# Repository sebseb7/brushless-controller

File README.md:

brushless-controller
====================

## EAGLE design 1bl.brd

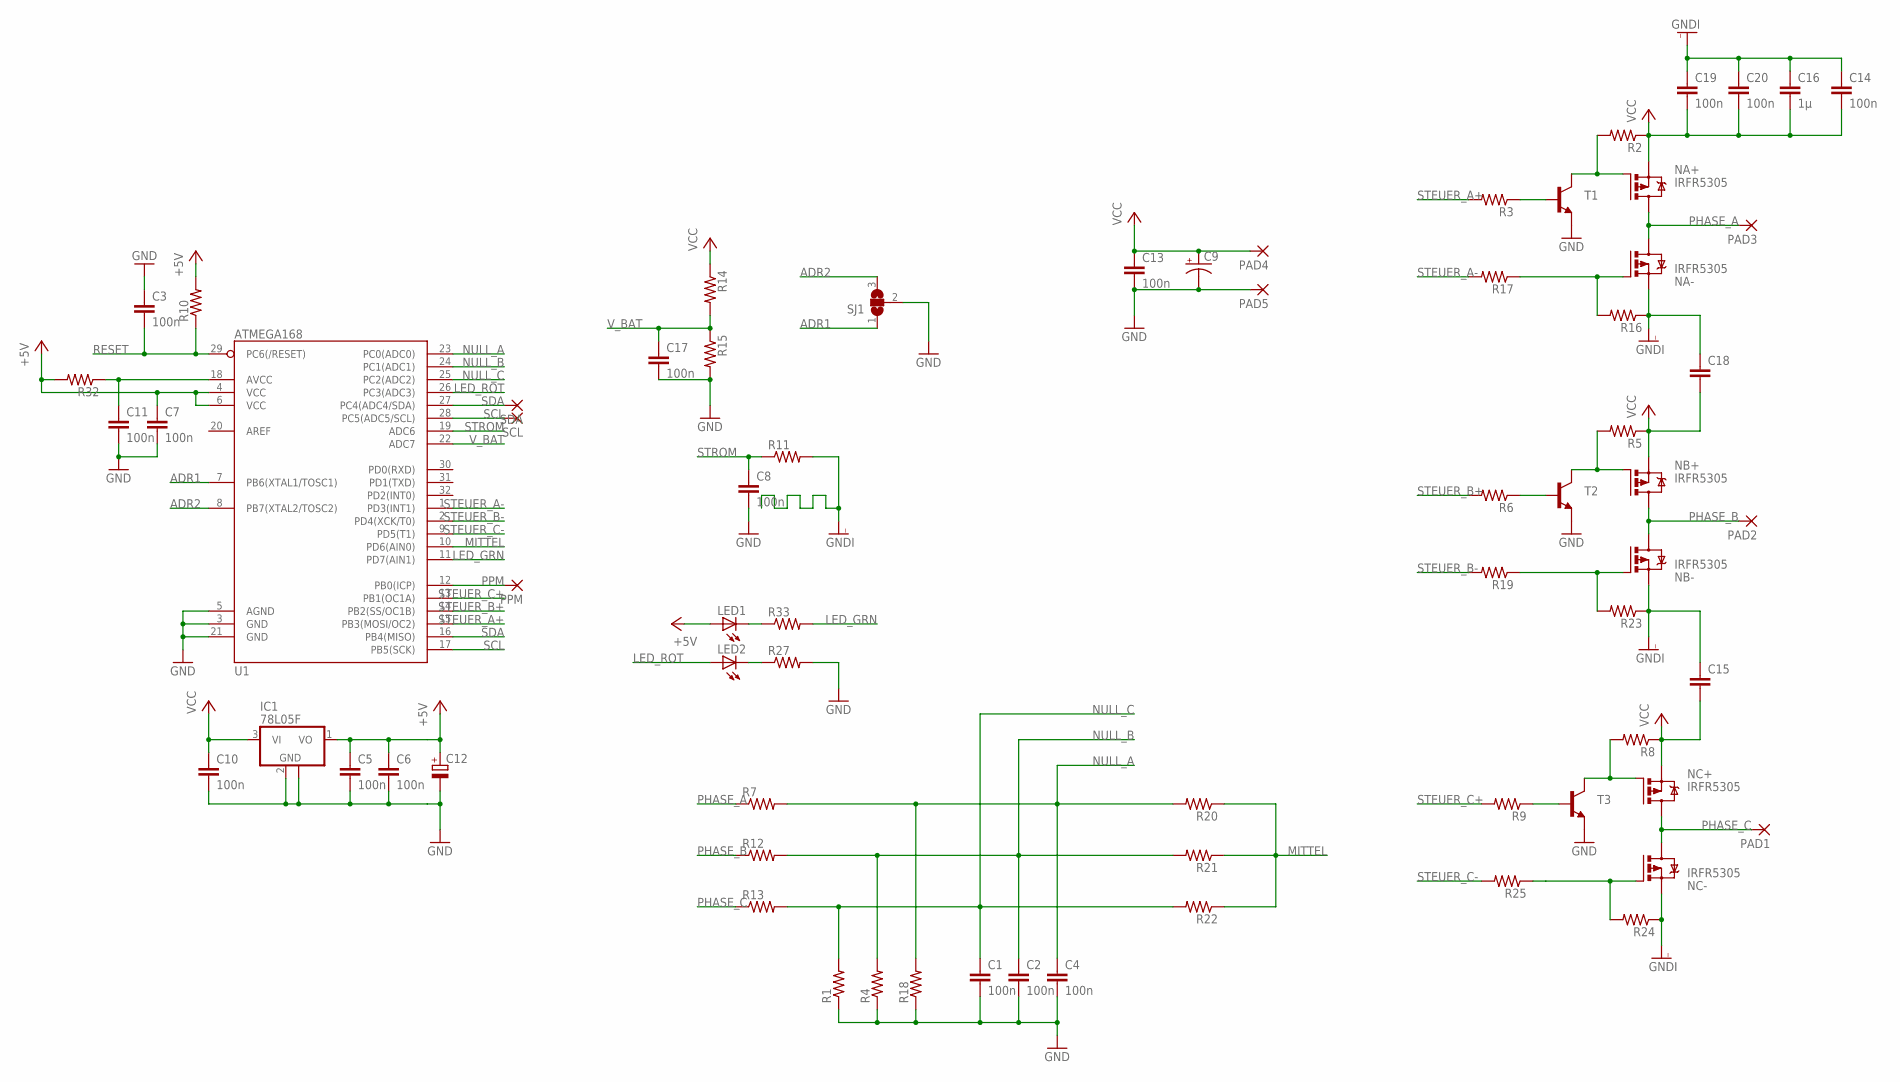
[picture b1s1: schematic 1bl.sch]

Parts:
C1, C2, C3, C4, C5, C6, C7, C8, C10, C11, C13, C14, C17, C19, C20: 100n; 0805
C9: CAP_POLPTH4; CPOL-RADIAL-1000UF-25V
C12: CPOL-EUB; PANASONIC_B
C15, C18: CAP0805; 0805
C16: 1µ; 0805
IC1: 78L05F; SOT89
LED1, LED2: LEDCHIP-LED0805; CHIP-LED0805
NA+: IRFR5305; D-PAK_TO252AA
NA-: IRFR5305; D-PAK_TO252AA
NB+: IRFR5305; D-PAK_TO252AA
NB-: IRFR5305; D-PAK_TO252AA
NC+: IRFR5305; D-PAK_TO252AA
NC-: IRFR5305; D-PAK_TO252AA
PAD1, PAD2, PAD3, PAD4, PAD5: SMD5; SMD2,54-5,08
PPM: SMD2; SMD1,27-2,54
R1, R2, R3, R4, R5, R6, R7, R8, R9, R10, R11, R12, R13, R14, R15, R16, R17, R18, R19, R20, R21, R22, R23, R24, R25, R27, R32, R33: RESISTOR; 0805
SCL: SMD2; SMD1,27-2,54
SDA: SMD2; SMD1,27-2,54
SJ1: SJ2W; SJ_2
T1, T2, T3: TRANSISTOR_NPNSOT23; SOT23
U1: ATMEGA168; TQFP32-08

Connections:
+5V: C5.1, C6.1, C7.1, C12.+, IC1.1 (VO), LED1.A, R10.2, R32.2, U1.4 (VCC), U1.6 (VCC)
ADR1: SJ1.1, U1.7 (PB6(XTAL1/TOSC1))
ADR2: SJ1.3, U1.8 (PB7(XTAL2/TOSC2))
GND: C1.2, C2.2, C3.1, C4.2, C5.2, C6.2, C7.2, C8.2, C9.2 (-), C10.2, C11.2, C12.-, C13.2, C17.2, IC1.2 (GND), IC1.2@1 (GND), PAD5.1, R1.1, R4.1, R15.2, R18.1, R27.2, SJ1.2, T1.2 (E), T2.2 (E), T3.2 (E), U1.3 (GND), U1.5 (AGND), U1.21 (GND)
GNDI: C14.1, C15.1, C16.1, C18.1, C19.1, C20.1, NA-.3 (S), NB-.3 (S), NC-.3 (S), R11.2, R16.1, R23.1, R24.1
LED_GRN: R33.2, U1.11 (PD7(AIN1))
LED_ROT: LED2.A, U1.26 (PC3(ADC3))
MITTEL: R20.1, R21.1, R22.1, U1.10 (PD6(AIN0))
unnamed: C11.1, R32.1, U1.18 (AVCC)
unnamed: NC+.1 (G), R8.2, T3.3 (C)
unnamed: NB+.1 (G), R5.2, T2.3 (C)
unnamed: NA+.1 (G), R2.2, T1.3 (C)
unnamed: LED1.C, R33.1
unnamed: LED2.C, R27.1
unnamed: NA-.1 (G), R16.2, R17.1
unnamed: NB-.1 (G), R19.1, R23.2
unnamed: NC-.1 (G), R24.2, R25.1
unnamed: R3.1, T1.1 (B)
unnamed: R6.1, T2.1 (B)
unnamed: R9.1, T3.1 (B)
NULL_A: C4.1, R7.2, R18.2, R20.2, U1.23 (PC0(ADC0))
NULL_B: C2.1, R4.2, R12.2, R21.2, U1.24 (PC1(ADC1))
NULL_C: C1.1, R1.2, R13.2, R22.2, U1.25 (PC2(ADC2))
PHASE_A: NA+.4 (D), NA-.4 (D), PAD3.1, R7.1
PHASE_B: NB+.4 (D), NB-.4 (D), PAD2.1, R12.1
PHASE_C: NC+.4 (D), NC-.4 (D), PAD1.1, R13.1
PPM: PPM.1, U1.12 (PB0(ICP))
RESET: C3.2, R10.1, U1.29 (PC6(/RESET))
SCL: SCL.1, U1.17 (PB5(SCK)), U1.28 (PC5(ADC5/SCL))
SDA: SDA.1, U1.16 (PB4(MISO)), U1.27 (PC4(ADC4/SDA))
STEUER_A+: R3.2, U1.15 (PB3(MOSI/OC2))
STEUER_A-: R17.2, U1.1 (PD3(INT1))
STEUER_B+: R6.2, U1.14 (PB2(SS/OC1B))
STEUER_B-: R19.2, U1.2 (PD4(XCK/T0))
STEUER_C+: R9.2, U1.13 (PB1(OC1A))
STEUER_C-: R25.2, U1.9 (PD5(T1))
STROM: C8.1, R11.1, U1.19 (ADC6)
VCC: C9.1 (+), C10.1, C13.1, C14.2, C15.2, C16.2, C18.2, C19.2, C20.2, IC1.3 (VI), NA+.3 (S), NB+.3 (S), NC+.3 (S), PAD4.1, R2.1, R5.1, R8.1, R14.1
V_BAT: C17.1, R14.2, R15.1, U1.22 (ADC7)

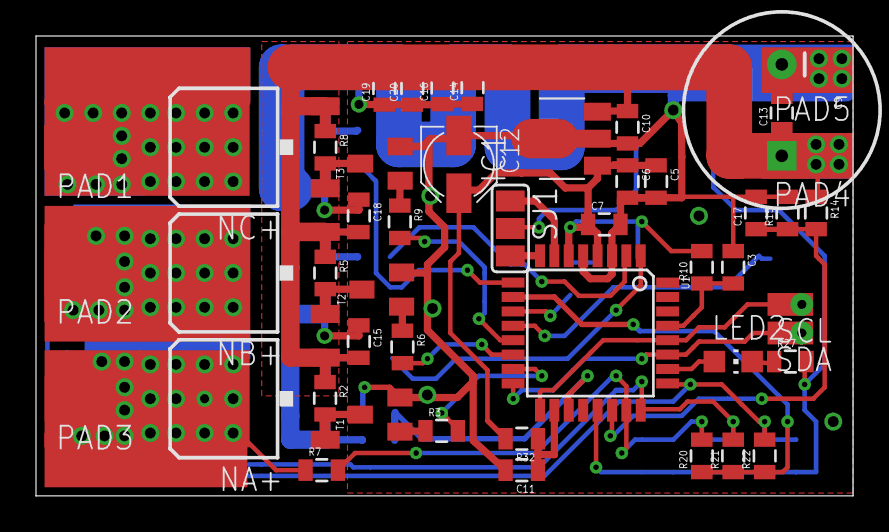
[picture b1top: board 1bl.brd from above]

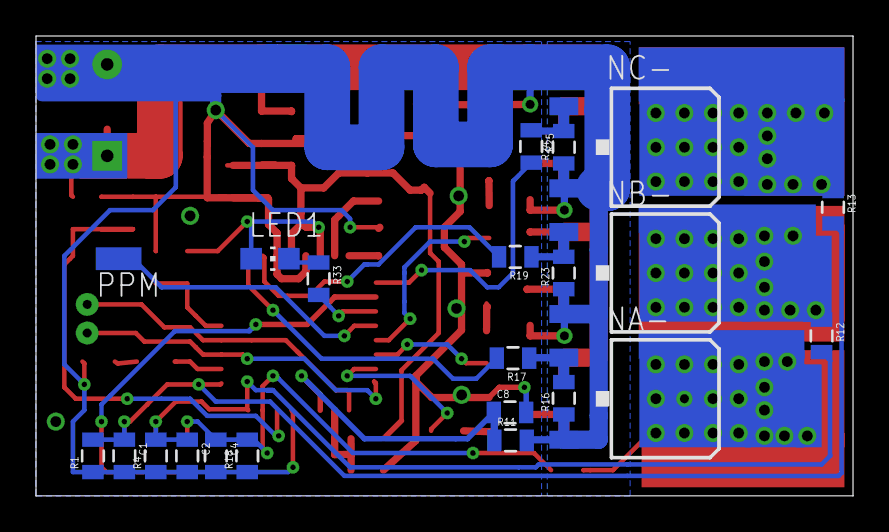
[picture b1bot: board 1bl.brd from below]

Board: 2 copper layers, 45.4 x 25.5 mm, 70 parts (22 on the bottom side), 39 nets.

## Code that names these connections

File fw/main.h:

#ifndef _MAIN_H
#define _MAIN_H

//#define MOTORADRESSE      0  // Adresse (1-4)     0 = Motoradresse über Lötjumper auf BL-Ctrl V1.1

#define MANUELL_PWM       0   // zur manuellen Vorgabe der PWM  Werte: 0-255
#define TEST_MANUELL      0   // zum Testen der Hardware ohne Kommutierungsdetektion  Werte: 0-255 (PWM)
#define TEST_SCHUB        0	  // Erzeugt ein Schubmuster        Werte: 0 = normal 1 = Test
#define POLANZAHL        12   // Anzahl der Pole (Magnete) Wird nur zur Drehzahlausgabe über Debug gebraucht
#define MAX_PWM         255
#define MIN_PWM           3
#define MIN_PPM          10   // ab hier (PPM-Signal) schaltet der Regler erst ein
#define FILTER_PPM        7   // wie stark soll das PPM-Signal gefiltert werden (Werte: 0-30)?

#define SIO_DEBUG         0   // Testwertausgaben auf der seriellen Schnittstelle
#define X3D_SIO           0	  // serielles Protokoll des X3D (38400Bd) Achtung: dann muss SIO_DEBUG = 0 sein

#define _16KHZ    // Schaltfrequenz  -- die gewünschte einkommentieren
//#define _32KHZ    // Schaltfrequenz  -- die gewünschte einkommentieren

//#define FDD6637_IRLR7843  1  // bessere MosFet bestückt? bewirkt höhere Stromgrenzen  


#ifdef _16KHZ
#if FDD_IRLR == 1                  // bessere Fets = mehr Strom zulassen
#define MAX_STROM        200  // ab ca. 20A PWM ausschalten
#define LIMIT_STROM      120  // ab ca. 12A PWM begrenzen
#else
#define MAX_STROM        130  // ab ca. 13A PWM ausschalten
#define LIMIT_STROM       65  // ab ca. 6,5A PWM begrenzen
#endif
#endif

#ifdef _32KHZ
#define MAX_STROM        130  // ab ca. 13A PWM ausschalten
#define LIMIT_STROM       50  // ab ca. 5,0A PWM begrenzen
#endif

#define SYSCLK	8000000L	//Quarz Frequenz in Hz

#define GRN_ON  {if(HwVersion < 12) PORTD |= GRUEN; else PORTD &= ~GRUEN;}
#define GRN_OFF {if(HwVersion > 11) PORTD |= GRUEN; else PORTD &= ~GRUEN;}


//Robbe Roxxy 2824-34 mit Todd 10x4,5 bei 16kHz
//PWM   Strom   Schub
//10   0,18A    21g
//20   0,30A    38g
//30   0,40A    49g
//40   0,54A    60g
//50   0,70A    83g
//60   0,95A   102g
//70   1,25A   128g
//80   1,50A   151g
//90   1,83A   175g
//100  2,25A   206g
//110  2,66A   228g
//120  3,10A   257g
//130  3,55A   278g
//140  4,00A   305g
//150  4,50A   330g
//160  5,30A   355g
//170  5,85A   387g
//180  6,40A   400g
//190  7,10A   425g
//200  7,60A   460g

//0,5A  63g 14%
//1,0A 110g 24%
//1,5A 170g 32%
//2,0A 195g 37%
//2,5A 230g 41%
//3,0A 260g 46%
//3,5A 290g 50%
//4,0A 310g 53%
//4,5A 340g 58%
//5,0A 360g 63%
//5,5A 380g 67%
//6,0A 400g 68%
//6,5A 420g 70%
//7,0A 450g 75%
//7,5A 460g 78%
//8,0A 475g 82%
//9,0A 550g 86%
//11 A 600g 100%


#include <stdio.h>
#include <stdlib.h>
#include <string.h>
#include <avr/io.h>
#include <avr/pgmspace.h>
#include <avr/interrupt.h>
#include <avr/eeprom.h>
#include <avr/boot.h>
#include <avr/wdt.h>

#include "twislave.h"
#include "old_macros.h"
#include "analog.h"
#include "uart.h"
#include "timer0.h"
#include "BLMC.h"

#include "PPM_Decode.h"

extern unsigned int  I2C_Timeout;
extern unsigned int SIO_Timeout;
extern unsigned int  PWM;
extern unsigned int  Strom;     //ca. in 0,1A
extern unsigned char Strom_max;
extern unsigned char Mittelstrom;
extern unsigned int  CntKommutierungen;
extern unsigned char MotorAnwerfen;
extern unsigned char MotorGestoppt;
extern unsigned char ZeitZumAdWandeln;
extern unsigned char MaxPWM;
extern unsigned char MotorAdresse; 
extern unsigned char PPM_Betrieb;
extern unsigned char HwVersion;
extern unsigned char IntRef;
#define ROT    0x08
#define GRUEN  0x80	

#define ADR1   0x40    // für Motoradresswahl
#define ADR2   0x80    // 

#if defined(__AVR_ATmega8__)
#  define OC1   PB1
#  define DDROC DDRB
#  define OCR   OCR1A
#  define PWM10 WGM10
#  define PWM11 WGM11
#endif 


#endif //_MAIN_H

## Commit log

2013-03-13 init
